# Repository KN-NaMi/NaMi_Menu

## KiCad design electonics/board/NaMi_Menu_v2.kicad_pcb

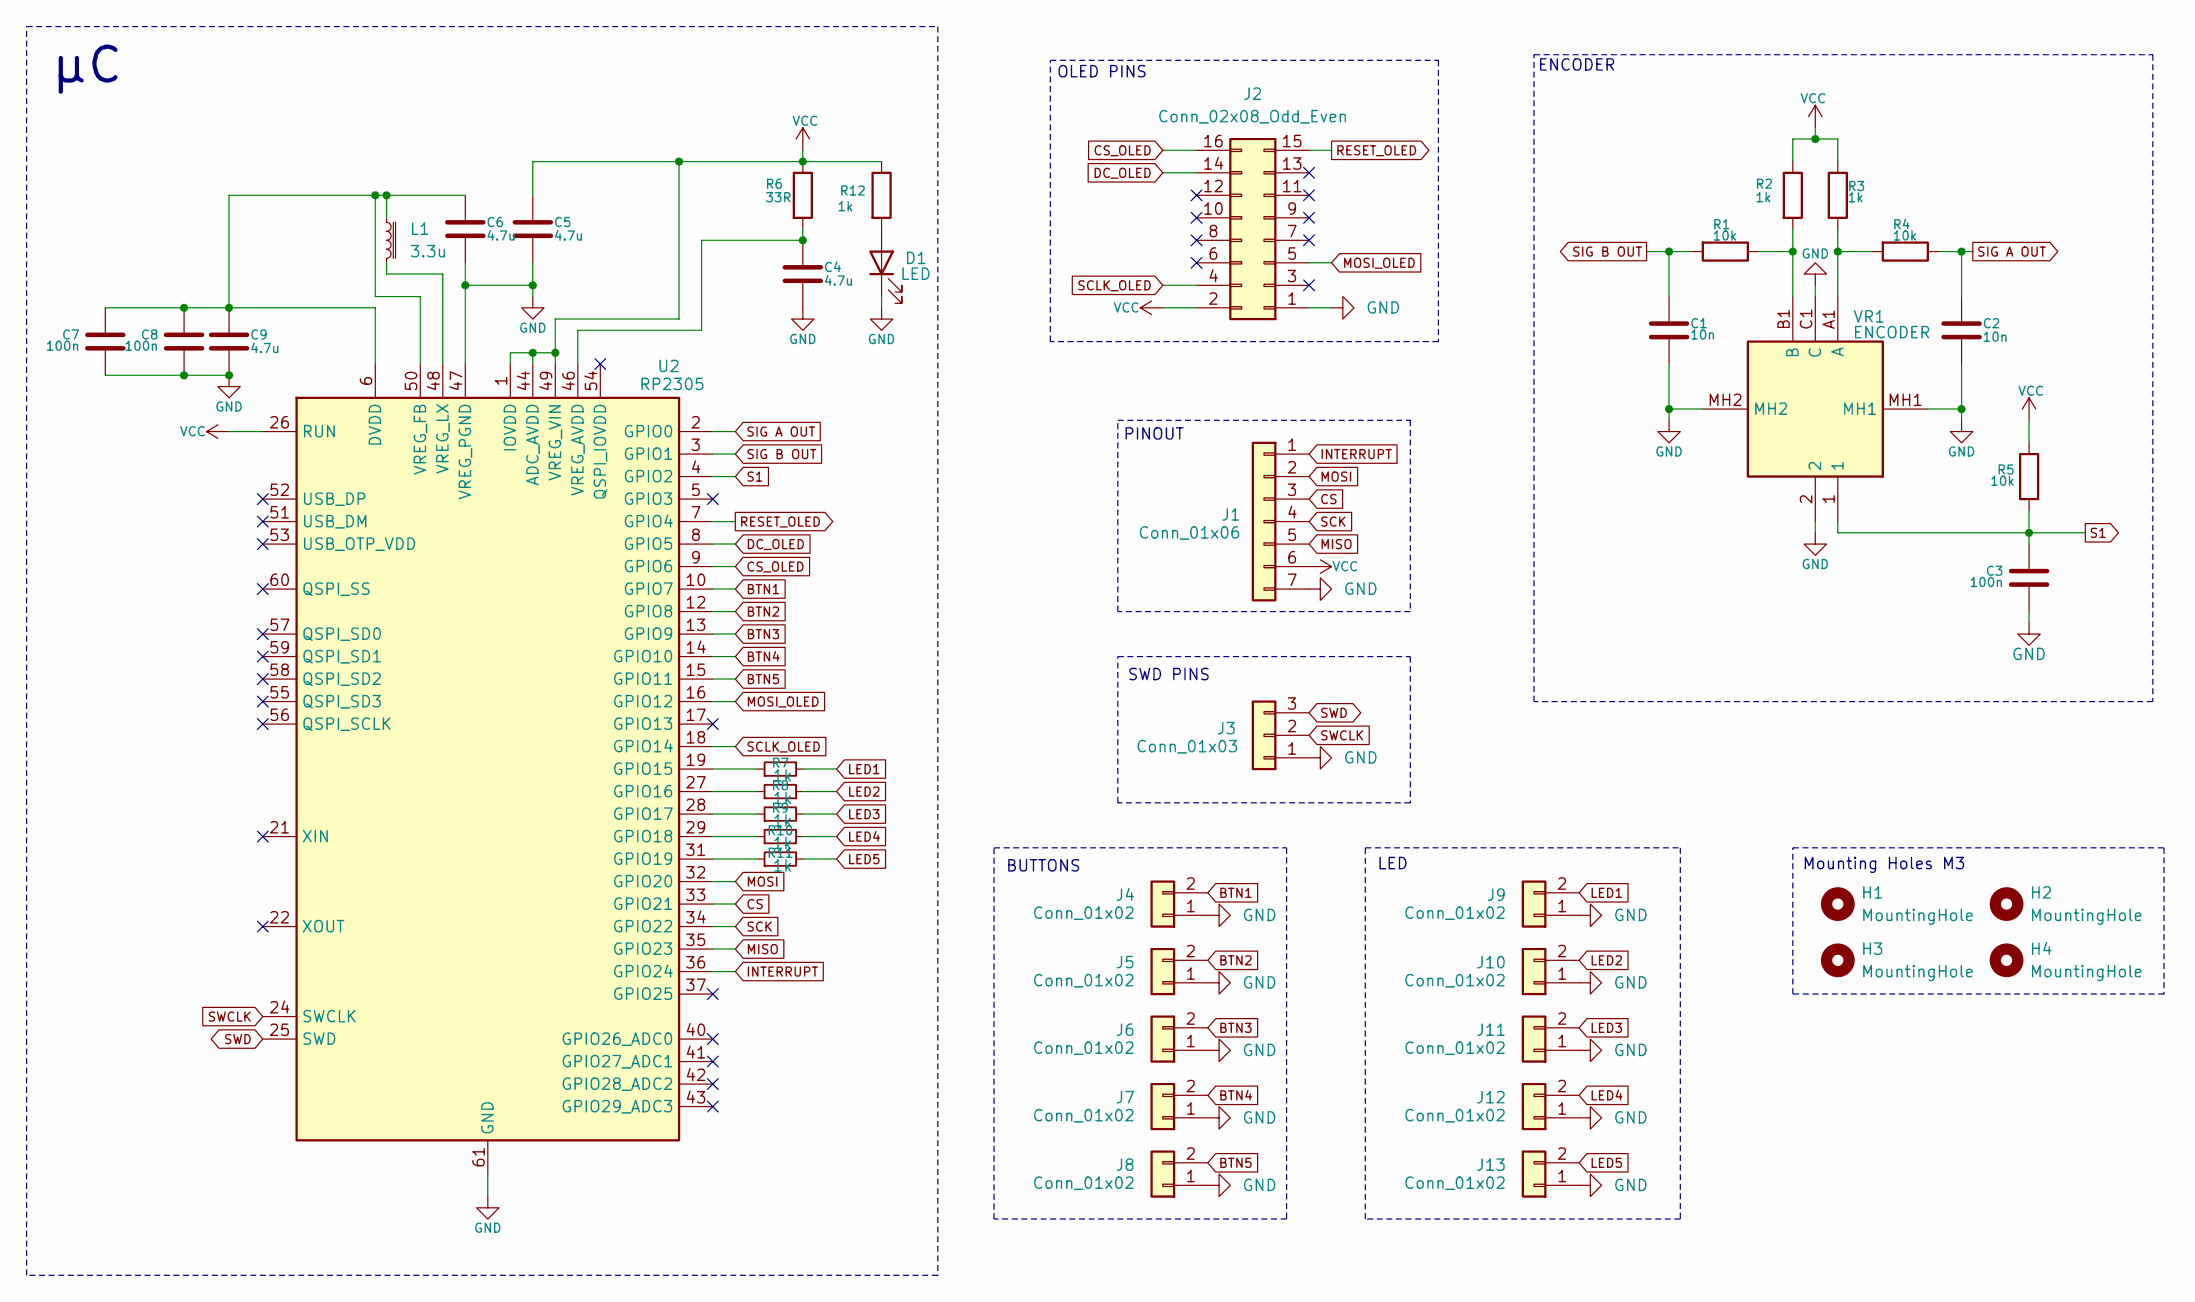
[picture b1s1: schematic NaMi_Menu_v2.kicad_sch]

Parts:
C1, C2: 10n; C_0805_2012Metric
C3, C7, C8: 100n; C_0805_2012Metric
C4, C5, C6, C9: 4.7u; C_0805_2012Metric
D1: LED; LED_0805_2012Metric
H1, H2, H3, H4: MountingHole; MountingHole_3.2mm_M3
J1: Conn_01x06; PinHeader_1x07_P2.54mm_Vertical
J2: Conn_02x08_Odd_Even; PinSocket_2x08_P2.54mm_Vertical
J3: Conn_01x03; PinHeader_1x03_P2.54mm_Vertical
J4, J5, J6, J7, J8, J9, J10, J11, J12, J13: Conn_01x02; PinHeader_1x02_P2.54mm_Vertical
L1: 3.3u; L_Neosid_SMs42
R1, R4, R5: 10k; R_0805_2012Metric
R2, R3, R7, R8, R9, R10, R11, R12: 1k; R_0805_2012Metric
R6: 33R; R_0805_2012Metric
U2: RP2305; QFN-60-1EP_7x7mm_P0.4mm_EP3.4x3.4mm
VR1: ENCODER; PEC11R4220FS0024; Mouser Part Number 652-PEC11R-4220F-S24

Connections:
BTN1: J4.2, U2.10 (GPIO7)
BTN2: J5.2, U2.12 (GPIO8)
BTN3: J6.2, U2.13 (GPIO9)
BTN4: J7.2, U2.14 (GPIO10)
BTN5: J8.2, U2.15 (GPIO11)
CS: J1.3, U2.33 (GPIO21)
CS_OLED: J2.16, U2.9 (GPIO6)
DC_OLED: J2.14, U2.8 (GPIO5)
GND: C1.2, C2.2, C3.2, C4.2, C5.2, C6.2, C7.2, C8.2, C9.2, D1.1 (K), J1.7, J2.1, J3.1, J4.1, J5.1, J6.1, J7.1, J8.1, J9.1, J10.1, J11.1, J12.1, J13.1, U2.47 (VREG_PGND), U2.61 (GND), VR1.2, VR1.C1 (C), VR1.MH1, VR1.MH2
INTERRUPT: J1.1, U2.36 (GPIO24)
LED1: J9.2, R7.2
LED2: J10.2, R8.2
LED3: J11.2, R9.2
LED4: J12.2, R10.2
LED5: J13.2, R11.2
MISO: J1.5, U2.35 (GPIO23)
MOSI: J1.2, U2.32 (GPIO20)
MOSI_OLED: J2.5, U2.16 (GPIO12)
unnamed: D1.2 (A), R12.2
unnamed: R7.1, U2.19 (GPIO15)
unnamed: R8.1, U2.27 (GPIO16)
unnamed: R9.1, U2.28 (GPIO17)
unnamed: R10.1, U2.29 (GPIO18)
unnamed: R11.1, U2.31 (GPIO19)
unnamed: C4.1, R6.2, U2.46 (VREG_AVDD)
unnamed: C6.1, C7.1, C8.1, C9.1, L1.1, U2.6 (DVDD), U2.23 (DVDD), U2.39 (DVDD), U2.50 (VREG_FB)
unnamed: L1.2, U2.48 (VREG_LX)
unnamed: R3.2, R4.2, VR1.A1 (A)
unnamed: R1.1, R2.2, VR1.B1 (B)
RESET_OLED: J2.15, U2.7 (GPIO4)
S1: C3.1, R5.2, U2.4 (GPIO2), VR1.1
SCK: J1.4, U2.34 (GPIO22)
SCLK_OLED: J2.4, U2.18 (GPIO14)
SIG A OUT: C2.1, R4.1, U2.2 (GPIO0)
SIG B OUT: C1.1, R1.2, U2.3 (GPIO1)
SWCLK: J3.2, U2.24 (SWCLK)
SWD: J3.3, U2.25 (SWD)
VCC: C5.1, J1.6, J2.2, R2.1, R3.1, R5.1, R6.1, R12.1, U2.1 (IOVDD), U2.11 (IOVDD), U2.20 (IOVDD), U2.26 (RUN), U2.30 (IOVDD), U2.38 (IOVDD), U2.44 (ADC_AVDD), U2.45 (IOVDD), U2.49 (VREG_VIN)

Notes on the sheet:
Mounting Holes M3
LED
OLED PINS
ENCODER
SWD PINS
BUTTONS
PINOUT

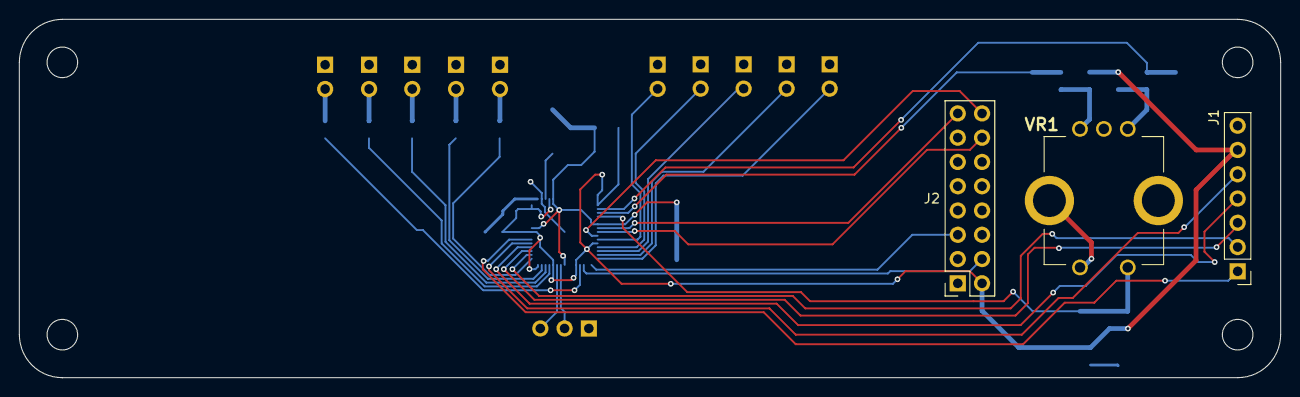
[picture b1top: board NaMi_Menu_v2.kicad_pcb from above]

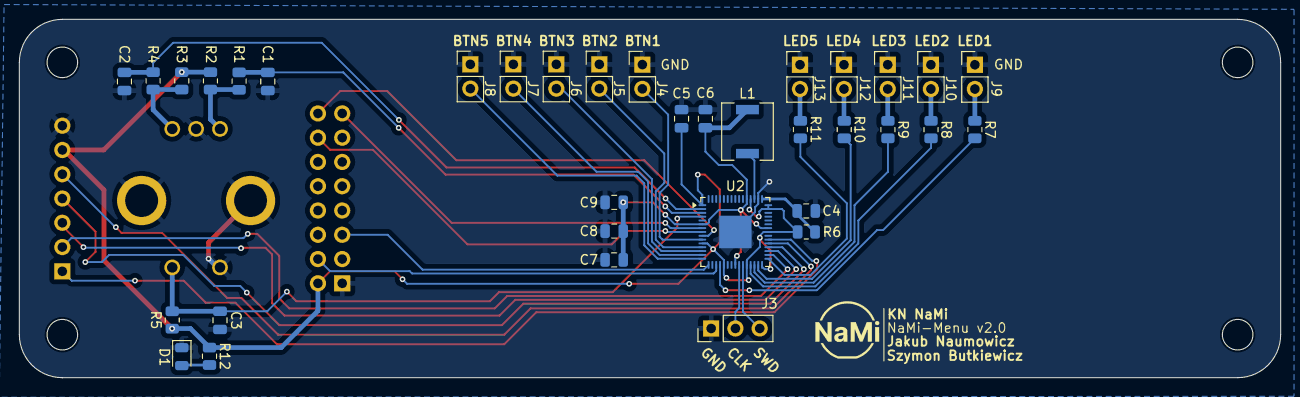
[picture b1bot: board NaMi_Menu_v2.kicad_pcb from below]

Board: 2 copper layers, 132.0 x 37.5 mm, 42 parts (35 on the bottom side), 38 nets.

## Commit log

2025-12-18 schemat-wersja1
2025-12-20 folder libs
2025-12-20 schemat wersja z SPI
2026-02-21 Schemat wersja z Interrupt
    Dodano wyjście interrupt, 5 miejsc na przyciski oraz 5 miejsc na diody LED. Dodano również LED sygnalizacyjny na zasilaniu.
2026-03-08 v2 board with MC
2026-03-13 Modified PCB design
2026-03-14 PCB Correction + Gerber files
